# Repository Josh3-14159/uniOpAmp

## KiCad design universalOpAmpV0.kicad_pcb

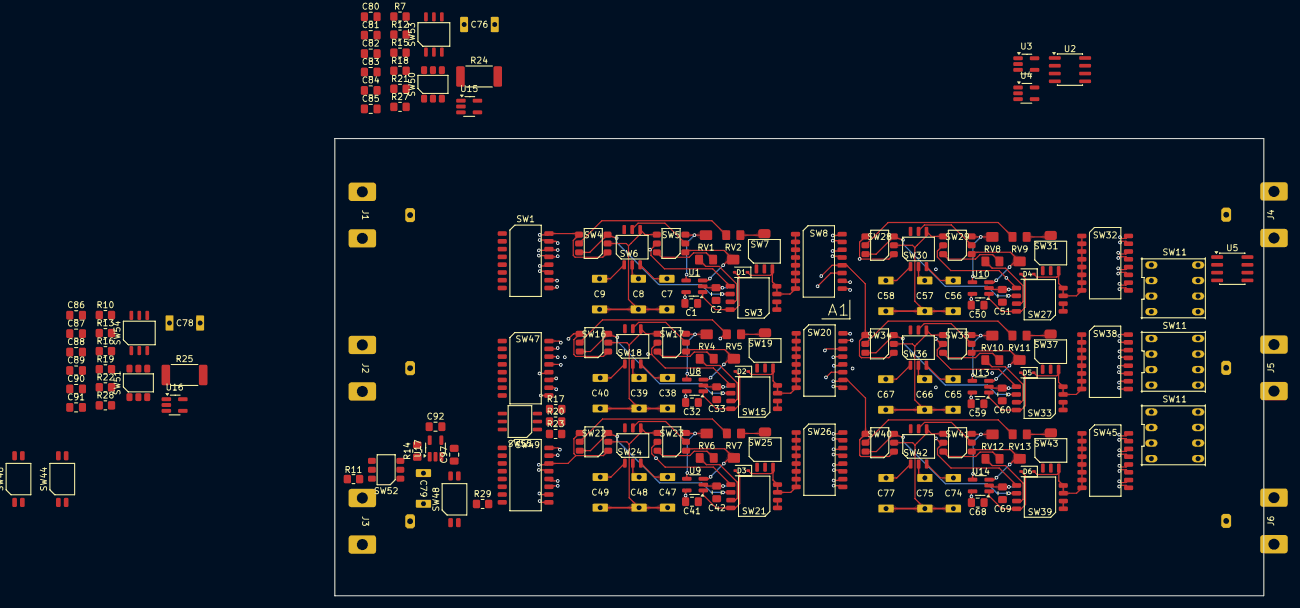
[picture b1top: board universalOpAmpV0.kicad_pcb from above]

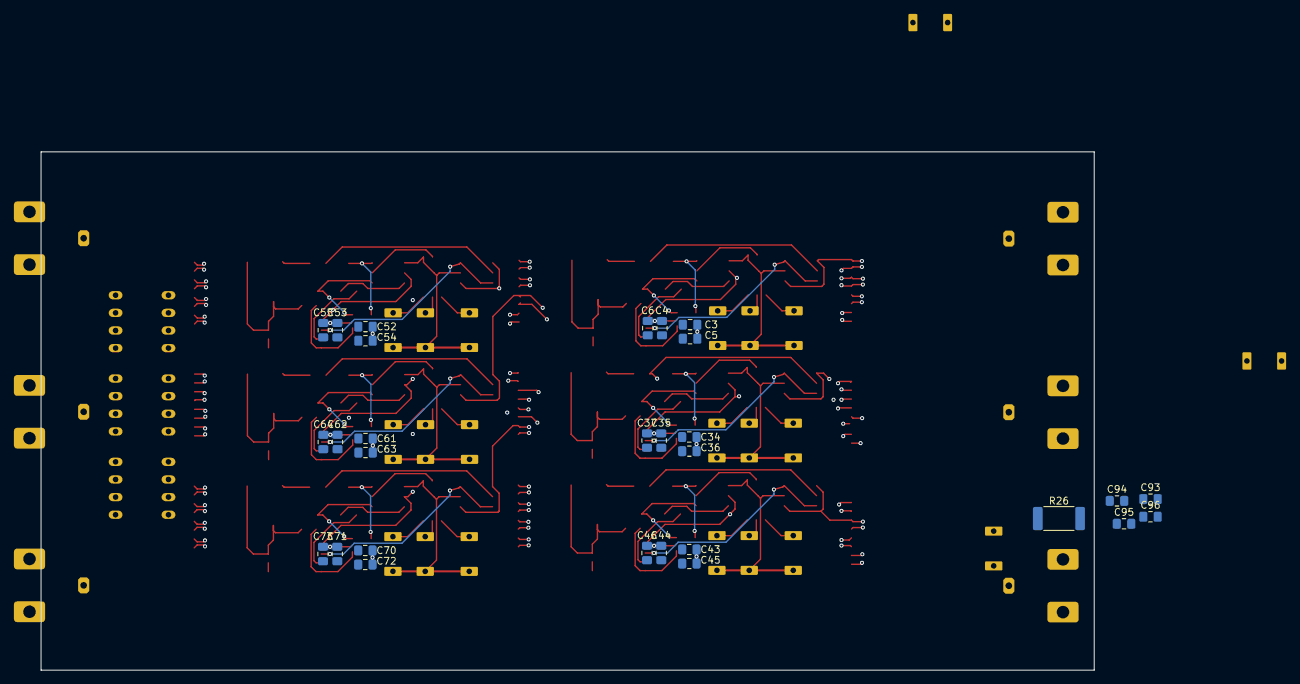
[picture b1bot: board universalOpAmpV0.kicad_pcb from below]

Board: 6 copper layers, 151.7 x 74.7 mm, 184 parts (29 on the bottom side), 134 nets.

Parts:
C1, C2, C3, C4, C5, C6, C32, C33, C34, C35, C36, C37, C41, C42, C43, C44, C45, C46, C50, C51, C52, C53, C54, C55, C59, C60, C61, C62, C63, C64, C68, C69, C70, C71, C72, C73, C80, C81, C82, C83, C84, C85, C86, C87, C88, C89, C90, C91, C92, C93, C94, C95, C96, C97: C; C_0805_Metric2012_HandSolder
C7, C8, C9, C38, C39, C40, C47, C48, C49, C56, C57, C58, C65, C66, C67, C74, C75, C77: C_Small; PP_CAP
C76, C78, C79: 100n; PP_CAP
D1, D2, D3, D4, D5, D6: 1N4148WS; D_SOD-323
J1, J2, J3, J4, J5, J6: BNC I1; BNC-0731000105
R7, R10, R11: 1M; R_0805_2012Metric_Pad1.20x1.40mm_HandSolder
R12, R13, R14, R15, R16, R17, R18, R19, R20, R21, R22, R23: R; R_0805_2012Metric_Pad1.20x1.40mm_HandSolder
R24, R25, R26: 50R; R_2512_6332Metric_Pad1.40x3.35mm_HandSolder
R27, R28, R29: 0R; R_0805_2012Metric_Pad1.20x1.40mm_HandSolder
RV1, RV2, RV4, RV5, RV6, RV7, RV8, RV9, RV10, RV11, RV12, RV13: R_Trim_Pot; PVG5H
SW1, SW8, SW20, SW26, SW32, SW38, SW45, SW47, SW49: 218-8LPSTR
SW3, SW15, SW21, SW27, SW33, SW39: 218-4LPSTR
SW4, SW5, SW16, SW17, SW22, SW23, SW28, SW29, SW34, SW35, SW40, SW41: SW_DPDT; CAS-DxxB
SW6, SW18, SW24, SW30, SW36, SW42, SW53, SW54, SW55: CS-4-14; CS-4-14NB
SW7, SW19, SW25, SW31, SW37, SW43: SW_SP3T; CS-4-13NB
SW11, SW11#2, SW11#3: SW_Rotary_1x7; SS-10-16
SW44, SW46, SW48: SW_DIP_x02; 218-2LPSTR
SW50, SW51, SW52: SW_DPDT_x2; CAS-DxxB
U1, U3, U4, U8, U9, U10, U13, U14, U15, U16, U17: OPA992DBV; SOT-23-5_HandSoldering
U2, U5: BUF634A; SOIC-8_3.9x4.9mm_P1.27mm

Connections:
+VDC: C1.1, C3.1, C5.1, C32.1, C34.1, C36.1, C41.1, C43.1, C45.1, C50.1, C52.1, C54.1, C59.1, C61.1, C63.1, C68.1, C70.1, C72.1, C80.1, C82.1, C84.1, C86.1, C88.1, C90.1, C92.1, C94.1, C96.1, U1.5 (V+), U2.7 (V+), U3.5 (V+), U4.5 (V+), U5.7 (V+), U8.5 (V+), U9.5 (V+), U10.5 (V+), U13.5 (V+), U14.5 (V+), U15.5 (V+), U16.5 (V+), U17.5 (V+)
-VDC: C2.2, C4.2, C6.2, C33.2, C35.2, C37.2, C42.2, C44.2, C46.2, C51.2, C53.2, C55.2, C60.2, C62.2, C64.2, C69.2, C71.2, C73.2, C81.2, C83.2, C85.2, C87.2, C89.2, C91.2, C93.2, C95.2, C97.2, U1.2 (V-), U2.4 (V-), U3.2 (V-), U4.2 (V-), U5.4 (V-), U8.2 (V-), U9.2 (V-), U10.2 (V-), U13.2 (V-), U14.2 (V-), U15.2 (V-), U16.2 (V-), U17.2 (V-)
/InputStage1/I: C76.1, J1.1 (In), R27.1, SW44.2
/InputStage2/I: C78.1, J2.1 (In), R28.1, SW46.2
/InputStage3/I: C79.1, J3.1 (In), R29.1, SW48.2
A1: D1.1 (K), SW3.3 (I), SW3.4 (I), SW7.3 (4), SW8.1, SW8.2, SW8.3, SW8.4, SW8.5, SW8.6, SW8.7, SW8.8, SW11#2.1
A2: D2.1 (K), SW11#2.2, SW15.3 (I), SW15.4 (I), SW19.3 (4), SW20.1, SW20.2, SW20.3, SW20.4, SW20.5, SW20.6, SW20.7, SW20.8
A3: D3.1 (K), SW11#2.3, SW21.3 (I), SW21.4 (I), SW25.3 (4), SW26.1, SW26.2, SW26.3, SW26.4, SW26.5, SW26.6, SW26.7, SW26.8
A4: D4.1 (K), SW11#2.4, SW27.3 (I), SW27.4 (I), SW31.3 (4), SW32.1, SW32.2, SW32.3, SW32.4, SW32.5, SW32.6, SW32.7, SW32.8
A5: D5.1 (K), SW11#2.5, SW33.3 (I), SW33.4 (I), SW37.3 (4), SW38.1, SW38.2, SW38.3, SW38.4, SW38.5, SW38.6, SW38.7, SW38.8
A6: D6.1 (K), SW11#2.6, SW39.3 (I), SW39.4 (I), SW43.3 (4), SW45.1, SW45.2, SW45.3, SW45.4, SW45.5, SW45.6, SW45.7, SW45.8
GND: C1.2, C2.1, C3.2, C4.1, C5.2, C6.1, C32.2, C33.1, C34.2, C35.1, C36.2, C37.1, C41.2, C42.1, C43.2, C44.1, C45.2, C46.1, C50.2, C51.1, C52.2, C53.1, C54.2, C55.1, C59.2, C60.1, C61.2, C62.1, C63.2, C64.1, C68.2, C69.1, C70.2, C71.1, C72.2, C73.1, C80.2, C81.1, C82.2, C83.1, C84.2, C85.1, C86.2, C87.1, C88.2, C89.1, C90.2, C91.1, C92.2, C93.1, C94.2, C95.1, C96.2, C97.1, J1.2 (Ext), J2.2 (Ext), J3.2 (Ext), J4.2 (Ext), J5.2 (Ext_2), J6.2 (Ext_2), R7.2, R10.2, R11.2, R15.2, R16.2, R17.2, R18.2, R19.2, R20.2, R21.2, R22.2, R23.2, R24.2, R25.2, R26.2, SW3.1 (I), SW3.2 (I), SW7.1, SW15.1 (I), SW15.2 (I), SW19.1, SW21.1 (I), SW21.2 (I), SW25.1, SW27.1 (I), SW27.2 (I), SW31.1, SW33.1 (I), SW33.2 (I), SW37.1, SW39.1 (I), SW39.2 (I), SW43.1
N1: SW1.15, SW3.5 (O), SW5.5 (B), SW20.15, SW26.15, SW38.15, SW45.15, SW47.15
N2: SW1.13, SW8.15, SW15.5 (O), SW17.5 (B), SW26.13, SW32.15, SW45.13, SW49.15
N3: SW8.13, SW20.13, SW21.5 (O), SW23.5 (B), SW32.13, SW38.13, SW47.13, SW49.13
N4: SW1.11, SW20.11, SW26.11, SW27.5 (O), SW29.5 (B), SW38.11, SW45.11, SW47.11
N5: SW1.9, SW8.11, SW26.9, SW32.11, SW33.5 (O), SW35.5 (B), SW45.9, SW49.11
N6: SW8.9, SW20.9, SW32.9, SW38.9, SW39.5 (O), SW41.5 (B), SW47.9, SW49.9
unnamed: C7.1, C8.1, C9.1, SW4.2 (B), SW5.6 (C), SW6.1
unnamed: C7.2, SW6.2
unnamed: C8.2, SW6.3
unnamed: C9.2, SW6.4
unnamed: C38.1, C39.1, C40.1, SW16.2 (B), SW17.6 (C), SW18.1
unnamed: C38.2, SW18.2
unnamed: C39.2, SW18.3
unnamed: C40.2, SW18.4
unnamed: C47.1, C48.1, C49.1, SW22.2 (B), SW23.6 (C), SW24.1
unnamed: C47.2, SW24.2
unnamed: C48.2, SW24.3
unnamed: C49.2, SW24.4
unnamed: C56.1, C57.1, C58.1, SW28.2 (B), SW29.6 (C), SW30.1
unnamed: C56.2, SW30.2
unnamed: C57.2, SW30.3
unnamed: C58.2, SW30.4
unnamed: C65.1, C66.1, C67.1, SW34.2 (B), SW35.6 (C), SW36.1
unnamed: C65.2, SW36.2
unnamed: C66.2, SW36.3
unnamed: C67.2, SW36.4
unnamed: C74.1, C75.1, C77.1, SW40.2 (B), SW41.6 (C), SW42.1
unnamed: C74.2, SW42.2
unnamed: C75.2, SW42.3
unnamed: C77.2, SW42.4
unnamed: D1.2 (A), SW3.8 (O), U1.1
unnamed: D2.2 (A), SW15.8 (O), U8.1
unnamed: D3.2 (A), SW21.8 (O), U9.1
unnamed: D4.2 (A), SW27.8 (O), U10.1
unnamed: D5.2 (A), SW33.8 (O), U13.1
unnamed: D6.2 (A), SW39.8 (O), U14.1
unnamed: R15.1, SW53.2
unnamed: R16.1, SW54.2
unnamed: R17.1, SW55.2
unnamed: R18.1, SW53.3
unnamed: R19.1, SW54.3
unnamed: R20.1, SW55.3
unnamed: R21.1, SW53.4
unnamed: R22.1, SW54.4
unnamed: R23.1, SW55.4
unnamed: RV1.1, SW5.4 (A)
unnamed: RV2.1, SW4.5 (B)
unnamed: RV2.3, SW7.C
unnamed: RV4.1, SW17.4 (A)
unnamed: RV5.1, SW16.5 (B)
unnamed: RV5.3, SW19.C
unnamed: RV6.1, SW23.4 (A)
unnamed: RV7.1, SW22.5 (B)
unnamed: RV7.3, SW25.C
unnamed: RV8.1, SW29.4 (A)
unnamed: RV9.1, SW28.5 (B)
unnamed: RV9.3, SW31.C
unnamed: RV10.1, SW35.4 (A)
unnamed: RV11.1, SW34.5 (B)
unnamed: RV11.3, SW37.C
unnamed: RV12.1, SW41.4 (A)
unnamed: RV13.1, SW40.5 (B)
unnamed: RV13.3, SW43.C
unnamed: SW3.6 (O), SW4.3 (C), SW4.4 (A)
unnamed: RV1.3, SW3.7 (O)
unnamed: SW5.2 (B), SW6.C
unnamed: U3.3 (+), U4.3 (+)
unnamed: SW11#2.C, U5.3 (V_{IN})
unnamed: SW15.6 (O), SW16.3 (C), SW16.4 (A)
unnamed: RV4.3, SW15.7 (O)
unnamed: SW17.2 (B), SW18.C
unnamed: SW21.6 (O), SW22.3 (C), SW22.4 (A)
unnamed: RV6.3, SW21.7 (O)
unnamed: SW23.2 (B), SW24.C
unnamed: SW27.6 (O), SW28.3 (C), SW28.4 (A)
unnamed: RV8.3, SW27.7 (O)
unnamed: SW29.2 (B), SW30.C
unnamed: SW33.6 (O), SW34.3 (C), SW34.4 (A)
unnamed: RV10.3, SW33.7 (O)
unnamed: SW35.2 (B), SW36.C
unnamed: SW39.6 (O), SW40.3 (C), SW40.4 (A)
unnamed: RV12.3, SW39.7 (O)
unnamed: SW41.2 (B), SW42.C
unnamed: C76.2, SW44.3, SW44.4, SW50.1 (A), U15.3 (+)
unnamed: R27.2, SW1.1, SW1.2, SW1.3, SW1.4, SW1.5, SW1.6, SW1.7, SW1.8, SW50.2 (B)
unnamed: R12.1, SW50.3 (C), U15.1
unnamed: R7.1, SW50.4 (A)
unnamed: SW44.1, SW50.5 (B)
unnamed: R24.1, SW50.6 (C)
unnamed: C78.2, SW46.3, SW46.4, SW51.1 (A), U16.3 (+)
unnamed: R28.2, SW47.1, SW47.2, SW47.3, SW47.4, SW47.5, SW47.6, SW47.7, SW47.8, SW51.2 (B)
unnamed: R13.1, SW51.3 (C), U16.1
unnamed: R10.1, SW51.4 (A)
unnamed: SW46.1, SW51.5 (B)
unnamed: R25.1, SW51.6 (C)
unnamed: C79.2, SW48.3, SW48.4, SW52.1 (A), U17.3 (+)
unnamed: R29.2, SW49.1, SW49.2, SW49.3, SW49.4, SW49.5, SW49.6, SW49.7, SW49.8, SW52.2 (B)
unnamed: R14.1, SW52.3 (C), U17.1
unnamed: R11.1, SW52.4 (A)
unnamed: SW48.1, SW52.5 (B)
unnamed: R26.1, SW52.6 (C)
unnamed: RV2.2, SW5.1 (A), U1.3 (+)
unnamed: RV1.2, SW5.3 (C), U1.4 (-)
unnamed: RV5.2, SW17.1 (A), U8.3 (+)
unnamed: RV4.2, SW17.3 (C), U8.4 (-)
unnamed: RV7.2, SW23.1 (A), U9.3 (+)
unnamed: RV6.2, SW23.3 (C), U9.4 (-)
unnamed: RV9.2, SW29.1 (A), U10.3 (+)
unnamed: RV8.2, SW29.3 (C), U10.4 (-)
unnamed: RV11.2, SW35.1 (A), U13.3 (+)
unnamed: RV10.2, SW35.3 (C), U13.4 (-)
unnamed: RV13.2, SW41.1 (A), U14.3 (+)
unnamed: RV12.2, SW41.3 (C), U14.4 (-)
unnamed: R12.2, SW53.C, U15.4 (-)
unnamed: R13.2, SW54.C, U16.4 (-)
unnamed: R14.2, SW55.C, U17.4 (-)
P1: SW1.16, SW4.1 (A), SW4.6 (C), SW20.16, SW26.16, SW38.16, SW45.16, SW47.16
P2: SW1.14, SW8.16, SW16.1 (A), SW16.6 (C), SW26.14, SW32.16, SW45.14, SW49.16
P3: SW8.14, SW20.14, SW22.1 (A), SW22.6 (C), SW32.14, SW38.14, SW47.14, SW49.14
P4: SW1.12, SW20.12, SW26.12, SW28.1 (A), SW28.6 (C), SW38.12, SW45.12, SW47.12
P5: SW1.10, SW8.12, SW26.10, SW32.12, SW34.1 (A), SW34.6 (C), SW45.10, SW49.12
P6: SW8.10, SW20.10, SW32.10, SW38.10, SW40.1 (A), SW40.6 (C), SW47.10, SW49.10
